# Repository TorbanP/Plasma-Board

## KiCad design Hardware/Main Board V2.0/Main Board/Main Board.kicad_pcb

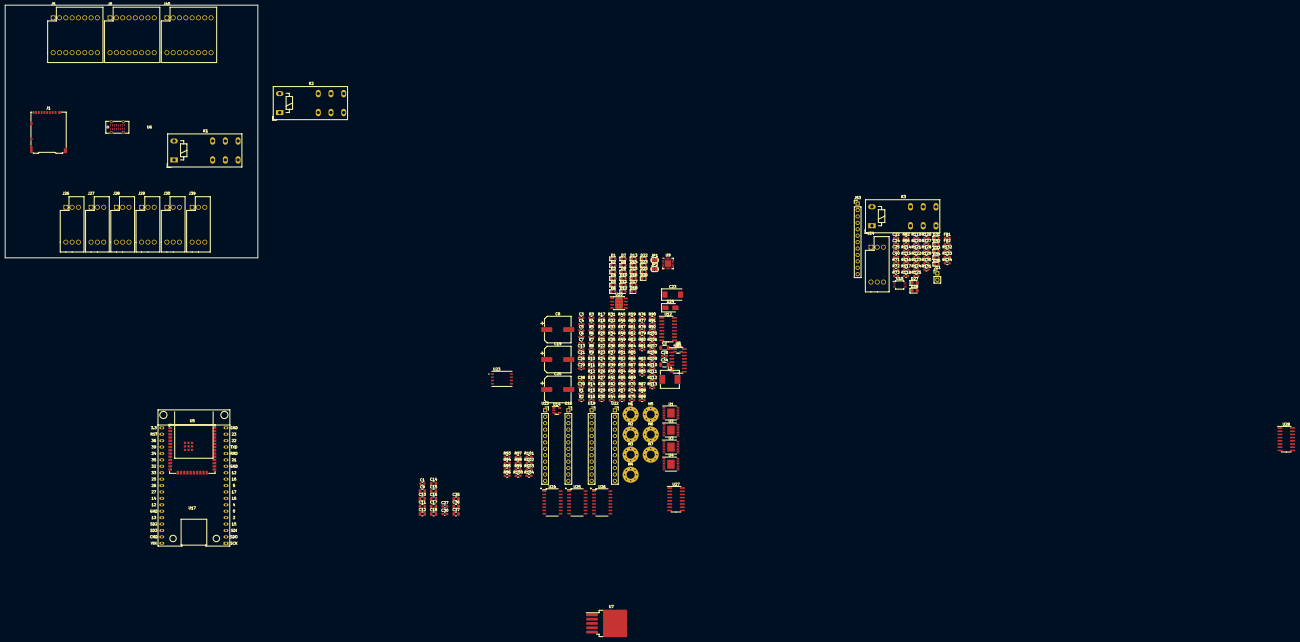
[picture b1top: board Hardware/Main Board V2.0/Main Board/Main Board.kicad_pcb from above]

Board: 2 copper layers, 100.0 x 100.0 mm, 254 parts (0 on the bottom side), 195 nets, no tracks yet.

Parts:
C1, C3, C4, C5, C6, C7, C13, C22, C24, C25, C26, C38, C40: 100nF; C_0603_1608Metric
C2, C34: 22uF; C_1206_3216Metric
C8, C19, C20: 120uF; CP_Elec_10x12.6
C9, C16, C36: 4.7uF; C_0805_2012Metric
C10, C12, C14, C15, C17, C35: 10uF; C_0805_2012Metric
C11, C18, C37: 1uF; C_0805_2012Metric
C21, C39: 10nF; C_0603_1608Metric
C23: 330uF; CP_EIA-7343-31_Kemet-D
C27: 22nf; C_0603_1608Metric_Pad1.08x0.95mm_HandSolder
C28, C30: 1uf; C_0603_1608Metric_Pad1.08x0.95mm_HandSolder
C29: 100nf; C_0603_1608Metric_Pad1.08x0.95mm_HandSolder
D1, D2, D3, D4, D5, D6, D7, D8, D9, D10, D11, D12, D13, D14, D15, D16, D17, D18, D22, D23, D25, D26, D31, D32, D33, D34, D35: Emerald; LED_0603_1608Metric
D24: SS54; D_SMA
D27, D28: MSCD104H; D_0805_2012Metric_Pad1.15x1.40mm_HandSolder
FB1, FB2: BLM18HE152SN1D; R_0603_1608Metric_Pad0.98x0.95mm_HandSolder
H1, H2, H3, H4, H5, H6, H7: MountingHole_3.2mm_M3_Pad_Via
J1: Micro_SD_Card; microSD_HC_Hirose_DM3AT-SF-PEJM5
J5, J8, J40: Conn_02x08_Top_Bottom; DB2ERH-2.5-2-8P-GN
J11: Conn_01x02_Male; PinHeader_1x02_P2.54mm_Vertical
J24, J26, J27, J28, J29, J30, J39: Conn_02x03_Top_Bottom; DB2ERH-2.5-2-3P-GN
J53: Module conn; PinHeader_1x12_P2.54mm_Vertical
JP1, JP2: SolderJumper_2_Bridged; SolderJumper-2_P1.3mm_Bridged_RoundedPad1.0x1.5mm
K1, K2, K3: G2RL-1-E-DC12; Relay_SPDT_Schrack-RT1-16A-FormC_RM5mm
L3: 15uH; L_Sunlord_MWSA0603S
R1, R2, R3, R4, R5, R6, R7, R8, R9, R10, R11, R12, R13, R14, R15, R16, R17, R18, R19, R20, R21, R50, R51, R79: 1K; R_0603_1608Metric
R22, R28, R29, R30, R31, R32, R33, R34, R35, R36, R37, R38, R39, R40, R41, R42, R43, R44, R45, R46, R47, R48, R49, R52, R53, R55, R71, R72, R80, R81, R82, R83, R86, R114, R115, R116, R117, R119, R120, R121, R122, R123, R124, R125, R126, R127, R128, R129, R130, R131: 10K; R_0603_1608Metric
R23, R54: 20R; R_0603_1608Metric
R24, R90, R91: 1K; R_0603_1608Metric_Pad0.98x0.95mm_HandSolder
R25: 120R; R_0603_1608Metric
R26: 24K; R_0603_1608Metric
R27: 47K; R_0603_1608Metric
R56, R57, R58, R59, R60, R61, R62, R63, R64, R65, R66, R67, R68, R69, R70, R105, R106, R107, R108, R109, R110, R111, R112, R113: 510R; R_0603_1608Metric
R73, R118: 5K; R_0603_1608Metric
R74, R75: 5.1K; R_0603_1608Metric
R76: 100K; R_0603_1608Metric
R77: 4.7K; R_0603_1608Metric
R78: 4.3K; R_0603_1608Metric
R84: 3.24K; R_0603_1608Metric
R85: 430R; R_0603_1608Metric
R87, R93, R94, R95, R96, R97, R98, R99, R100, R101, R102, R103, R104: 2K; R_0603_1608Metric_Pad0.98x0.95mm_HandSolder
R88, R89: 200; R_0603_1608Metric_Pad0.98x0.95mm_HandSolder
R92, R132, R133, R134: 2.4K; R_0603_1608Metric_Pad0.98x0.95mm_HandSolder
U1, U2, U3, U4: 74AHCT595PW; TSSOP-16-1EP_4.4x5mm_P0.65mm
U5: ESP32-WROOM-32UE-H4; ESP32-WROOM-32UE
U6: GT-USB-7051A
U7: LM2596S-12; TO-263-5_TabPin3
U8: AP2112K-3.3; SOT-23-5
U9: CP2104; QFN-24-1EP_4x4mm_P0.5mm_EP2.6x2.6mm
U10: TPS5430DDA; TI_SO-PowerPAD-8_ThermalVias
U11, U27, U28: ULN2003A; SOIC-16_3.9x9.9mm_P1.27mm
U12: 74LVC157A; SOP-16_3.9x9.9mm_P1.27mm
U13: Module A1; PinSocket_1x12_P2.54mm_Vertical
U14: NCV8114ASN150T1G; TSOT-23-5
U15: ADS1115IDGS; TSSOP-10_3x3mm_P0.5mm
U16: Module A2; PinSocket_1x12_P2.54mm_Vertical
U17: ESP32_38p; MH ET LIVE ESP-32 Dev Kit
U19: Module A3; PinSocket_1x12_P2.54mm_Vertical
U22: Module A4; PinSocket_1x12_P2.54mm_Vertical
U23: XTSD04GLGEAG; SON127P600X800X95-8N
U24, U25, U26: ELQ3H7; ELQ3H7 SOP-16_4.4x10.4mm_P1.27mm

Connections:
+3V3: C2.1, C3.1, C9.1, C11.1, C13.1, C15.1, C18.1, C22.1, J1.4 (VDD), R22.2, R28.2, R50.2, R51.2, R52.2, R55.2, R71.2, R72.2, R77.2, R78.2, R120.1, R121.1, R122.1, R123.1, R124.1, R125.1, R126.1, R127.1, R128.1, R129.1, R130.1, R131.1, U5.2 (3V3), U8.5 (VOUT), U9.5 (VIO), U9.6 (VDD), U9.7 (REGIN), U17.20 (3.3V), U23.8 (VDD)
+12V: C1.2, C2.2, C3.2, C4.1, C4.2, C5.1, C5.2, C6.1, C6.2, C7.1, C7.2, C8.2, C9.2, C10.1, C10.2, C11.2, C12.2, C13.2, C14.2, C15.2, C16.2, C17.2, C18.2, C19.2, C20.1, C20.2, C22.2, C23.1, C23.2, C24.2, C25.2, C26.1, C26.2, C40.2, D22.1 (K), D23.1 (K), D24.2 (A), D25.1 (K), D26.1 (K), H1.1, H2.1, H3.1, H4.1, H5.1, H6.1, H7.1, J1.6 (VSS), J1.9 (SHIELD), J24.3, J24.6, J26.1, J26.3, J26.4, J26.6, J27.1, J27.3, J27.4, J27.6, J28.1, J28.3, J28.4, J28.6, J29.1, J29.3, J29.4, J29.6, J30.1, J30.3, J30.4, J30.6, J39.1, J39.3, J39.4, J39.6, K1.A2, K2.A2, K3.A2, L3.2, R1.2, R2.2, R3.2, R4.2, R5.2, R6.2, R7.2, R8.2, R9.2, R10.2, R11.2, R12.2, R13.2, R14.2, R15.2, R16.2, R17.2, R18.2, R19.2, R20.2, R21.2, R27.1, R29.1, R30.1, R31.1, R32.1, R33.1, R34.1, R35.1, R36.1, R37.1, R38.1, R39.1, R40.1, R41.1, R42.1, R43.1, R44.1, R45.1, R46.1, R47.1, R48.1, R49.1, R53.1, R74.1, R75.1, R76.2, R79.2, R82.2, R83.2, R84.1, R85.2, R93.1, R94.1, R95.1, R96.1, R97.1, R98.1, R99.1, R100.1, R101.1, R102.1, R103.1, R104.1, R114.1, R115.1, R117.2, R119.1, U1.8 (GND), U1.10 (MR#), U1.13 (OE#), U1.16 (VCC), U2.8 (GND), U2.10 (MR#), U2.13 (OE#), U2.16 (VCC), U3.8 (GND), U3.10 (MR#), U3.13 (OE#), U3.16 (VCC), U4.8 (GND), U4.10 (MR#), U4.13 (OE#), U4.16 (VCC), U5.1 (GND), U5.15 (GND), U5.38 (GND), U5.39 (GND_THERMAL), U6.A1 (GND), U6.A12 (GND), U6.B1 (GND), U6.B12 (GND), U7.3 (GND), U7.5 (~ON/OFF), U8.1 (VIN), U8.2 (GND), U9.2 (GND), U9.25 (GND), U10.6 (GND), U10.9 (GNDPAD), U11.8 (GND), U11.9 (COM), U12.8 (GND), U12.15 (~EN), U12.16 (VCC), U13.1 (Gnd), U13.2 (VMot), U13.12 (Gnd), U16.1 (Gnd), U16.2 (VMot), U16.12 (Gnd), U17.13 (GND), U17.19 (GND), U17.33 (GND), U17.38 (VIN), U19.1 (Gnd), U19.2 (VMot), U19.12 (Gnd), U22.1 (Gnd), U22.2 (VMot), U22.12 (Gnd), U23.4 (VSS), U24.9, U24.11, U24.13, U24.15, U25.9, U25.11, U25.13, U25.15, U26.9, U26.11, U26.13, U26.15, U27.8 (GND), U27.9 (COM), U28.8 (GND), U28.9 (COM)
+24V: C8.1, C12.1, C14.1, C17.1, U7.1 (VIN), U10.7 (VIN)
A_Dir: R37.2, U2.4 (Q4), U11.6 (I6)
A_Dir_HV: D13.1 (K), J40.13, U11.11 (O6)
A_Enable: R39.2, U2.7 (Q7), U11.4 (I4)
A_Enable_HV: D11.1 (K), J40.9, U11.13 (O4)
A_LIM: R128.2, U5.10 (DAC_1/ADC2_CH8/GPIO25), U17.28 (IO25), U26.16
A_Step: R38.2, U2.5 (Q5), U11.5 (I5)
A_Step_HV: D12.1 (K), J40.11, U11.12 (O5)
B_Dir: R47.2, U3.1 (Q1), U28.3 (I3)
B_Dir_HV: D17.1 (K), J5.13, U28.14 (O3)
B_Enable: R49.2, U3.15 (Q0), U28.1 (I1)
B_Enable_HV: D15.1 (K), J5.9, U28.16 (O1)
B_LIM: R129.2, U5.11 (DAC_2/ADC2_CH9/GPIO26), U17.29 (IO26), U26.14
B_Step: R48.2, U3.2 (Q2), U28.2 (I2)
B_Step_HV: D16.1 (K), J5.11, U28.15 (O2)
CC1: R74.2, U6.A5 (CC1)
CC2: R75.2, U6.B5 (CC2)
CS_SD: J1.2 (DAT3/CD), U5.23 (MTDO/GPIO15/ADC2_CH3), U17.4 (IO15), U23.6 (SD0/DO)
C_Dir: R44.2, U3.4 (Q4), U28.6 (I6)
C_Dir_HV: D32.1 (K), J8.13, U28.11 (O6)
C_Enable: R46.2, U3.7 (Q7), U28.4 (I4)
C_Enable_HV: D18.1 (K), J8.9, U28.13 (O4)
C_LIM: R130.2, U5.12 (ADC2_CH7/GPIO27), U17.30 (IO27), U26.12
C_Step: R45.2, U3.5 (Q5), U28.5 (I5)
C_Step_HV: D31.1 (K), J8.11, U28.12 (O5)
D+: U6.A6 (DP1), U6.B6 (DP2), U9.3 (D+)
D-: U6.A7 (DN1), U6.B7 (DN2), U9.4 (D-)
DTR: R81.1, U9.23 (~DTR)
EXT_MUX_EN: R119.2, U12.1 (S)
GPI_0: C24.1, JP1.2 (B), R22.1, R120.2, U5.25 (GPIO0/BOOT/ADC2_CH1), U17.6 (IO0), U24.16
I2S_BCK: U1.11 (SHCP), U2.11 (SHCP), U3.11 (SHCP), U4.11 (SHCP), U5.37 (GPIO23), U17.18 (IO23)
I2S_DATA: U1.14 (DS), U5.36 (GPIO22), U17.17 (IO22)
I2S_WS: U1.12 (STCP), U2.12 (STCP), U3.12 (STCP), U4.12 (STCP), U5.33 (GPIO21), U17.14 (IO21)
MACRO_1: R122.2, U5.4 (SENSOR_VP/GPIO36/ADC1_CH0), U17.22 (IO36), U24.12
MACRO_2: R123.2, U5.5 (SENSOR_VN/GPIO39/ADC1_CH3), U17.23 (IO39), U24.10
MACRO_3: R124.2, U5.6 (GPIO34/ADC1_CH6), U17.24 (IO34), U25.16
MISO: J1.7 (DAT0), U5.14 (MTDI/GPIO12/ADC2_CH5), U17.32 (IO12)
MOSI: J1.3 (CMD), U5.16 (MTCK/GPIO13/ADC2_CH4), U17.34 (IO13), U23.5 (CMD/DI)
unnamed: D1.2 (A), R10.1
unnamed: D2.2 (A), R1.1
unnamed: D3.2 (A), R2.1
unnamed: D4.2 (A), R3.1
unnamed: D5.2 (A), R4.1
unnamed: D6.2 (A), R5.1
unnamed: D7.2 (A), R6.1
unnamed: D8.2 (A), R7.1
unnamed: D9.2 (A), R8.1
unnamed: D10.2 (A), R9.1
unnamed: D11.2 (A), R11.1
unnamed: D12.2 (A), R12.1
unnamed: D13.2 (A), R13.1
unnamed: D14.2 (A), R14.1
unnamed: D15.2 (A), R15.1
unnamed: D16.2 (A), R16.1
unnamed: D17.2 (A), R17.1
unnamed: D18.2 (A), R18.1
unnamed: U6.A4 (VBUS), U6.A9 (VBUS), U6.B4 (VBUS), U6.B9 (VBUS)
unnamed: D22.2 (A), R78.1
unnamed: D23.2 (A), R79.1
unnamed: C21.2, D24.1 (K), L3.1, U10.8 (PH)
unnamed: D25.2 (A), R85.1
unnamed: D27.2 (A), R24.1, R88.2
unnamed: C29.1, D27.1 (K), FB2.1, R132.1, R133.1, R134.1, U14.1 (IN), U14.3 (EN), U15.8 (VDD)
unnamed: C28.2, C29.2, D28.2 (A), FB1.2, R92.2, U14.2 (GND), U15.3 (GND)
unnamed: D28.1 (K), R87.2, R89.2
unnamed: D31.2 (A), R19.1
unnamed: D32.2 (A), R20.1
unnamed: D33.2 (A), R21.1
unnamed: D34.2 (A), R50.1
unnamed: D35.2 (A), R51.1
unnamed: J24.4, R23.1
unnamed: J24.5, R54.1
unnamed: R106.1, R107.1, R108.1, R109.1
unnamed: R110.1, R111.1, R112.1, R113.1
unnamed: R56.1, R57.1, R58.1, R105.1
unnamed: J5.2, R106.2
unnamed: J5.4, R107.2
unnamed: J5.6, R108.2
unnamed: J5.8, R109.2
unnamed: J5.10, R63.2
unnamed: J5.12, R64.2
unnamed: J5.14, R65.2
unnamed: J5.16, R66.2
unnamed: R59.1, R60.1, R61.1, R62.1
unnamed: R63.1, R64.1, R65.1, R66.1
unnamed: J8.2, R110.2
unnamed: J8.4, R111.2
unnamed: J8.6, R112.2
unnamed: J8.8, R113.2
unnamed: J8.10, R59.2
unnamed: J8.12, R60.2
unnamed: J8.14, R61.2
unnamed: J8.16, R62.2
unnamed: J11.1, R24.2
unnamed: J11.2, R87.1
unnamed: J26.2, U24.8
unnamed: J26.5, U24.6
unnamed: J27.2, U25.4
unnamed: J27.5, U25.2
unnamed: J28.2, U25.8
unnamed: J28.5, U25.6
unnamed: J29.2, U26.4
unnamed: J29.5, U26.2
unnamed: J30.2, U26.8
unnamed: J30.5, U26.6
unnamed: R67.1, R68.1, R69.1, R70.1
unnamed: J39.2, U24.4
unnamed: J39.5, U24.2
unnamed: J40.2, R56.2
unnamed: J40.4, R57.2
unnamed: J40.6, R58.2
unnamed: J40.8, R105.2
unnamed: J40.10, R67.2
unnamed: J40.12, R68.2
unnamed: J40.14, R69.2
unnamed: J40.16, R70.2
unnamed: C30.2, FB1.1, J53.1, J53.12
unnamed: C30.1, FB2.2, J53.3
unnamed: J53.9, R134.2, U15.2 (ALERT/RDY)
unnamed: J53.10, R132.2, U15.9 (SDA)
unnamed: J53.11, R133.2, U15.10 (SCL)
unnamed: R93.2, U24.1
unnamed: R94.2, U24.3
unnamed: R95.2, U24.5
unnamed: R96.2, U24.7
unnamed: R97.2, U25.1
unnamed: R98.2, U25.3
unnamed: R99.2, U25.5
unnamed: R100.2, U25.7
unnamed: R101.2, U26.1
unnamed: R102.2, U26.3
unnamed: R103.2, U26.5
unnamed: R104.2, U26.7
unnamed: R131.2, U26.10
unnamed: U1.9 (Q7S), U2.14 (DS)
unnamed: U2.9 (Q7S), U3.14 (DS)
unnamed: U3.9 (Q7S), U4.14 (DS)
unnamed: C19.1, U7.4 (FB)
unnamed: R76.1, U8.3 (EN)
unnamed: R26.1, R27.2, U9.8 (VBUS)
unnamed: C16.1, U9.16 (VPP)
unnamed: R77.1, U9.9 (~RST)
unnamed: C21.1, U10.1 (BOOT)
unnamed: R83.1, R84.2, U10.4 (VSENSE)
unnamed: C28.1, R90.1, R91.2, U14.5 (OUT)
unnamed: R92.1, U15.1 (ADDR)
unnamed: C27.1, R88.1, R90.2, U15.4 (AIN0)
unnamed: C27.2, R89.1, R91.1, U15.5 (AIN1)
unnamed: R25.1, R53.2, R54.2
unnamed: R23.2, R25.2, R52.1
unnamed: C1.1, R86.2
unnamed: R73.2, R82.1
unnamed: C40.1, R116.2
unnamed: R117.1, R118.2
PWM1: R86.1, R114.2, U5.24 (ADC2_CH2/GPIO2), U17.5 (IO2)
PWM2: R115.2, R116.1, U5.26 (ADC2_CH0/GPIO4), U17.7 (IO4)
RESET: C25.1, JP2.2 (B), R28.1, R121.2, U5.3 (EN/CHIP_PU), U17.21 (RST), U24.14
RLY_1: R29.2, U1.3 (Q3), U27.7 (I7)
RLY_1_HV: D7.1 (K), K2.A1, U27.10 (O7)
RLY_2: R36.2, U2.6 (Q6), U11.7 (I7)
RLY_2_HV: D14.1 (K), K1.A1, U11.10 (O7)
RLY_3: R43.2, U2.3 (Q3), U28.7 (I7)
RLY_3_HV: K3.A1, U28.10 (O7)
RS485_EN: R72.1, U5.29 (GPIO5), U17.10 (IO5)
RS485_RX: D35.1 (K), R71.1, U5.27 (GPIO16), U17.8 (IO16)
RS485_TX: D34.1 (K), R55.1, U5.28 (GPIO17), U17.9 (IO17)
RTS: R80.1, U9.19 (~RTS)
RXD0: U5.34 (U0RXD/GPIO3), U9.21 (TXD), U17.15 (RXD)
SCL: U5.31 (GPIO19), U17.12 (IO19)
SCLK: J1.5 (CLK), U5.13 (MTMS/GPIO14/ADC2_CH6), U17.31 (IO14), U23.3 (CLK)
SDA: U5.30 (GPIO18), U17.11 (IO18)
TXD0: U5.35 (U0TXD/GPIO1), U9.20 (RXD), U17.16 (TXD)
X_Dir: R33.2, U1.1 (Q1), U27.3 (I3)
X_Dir_HV: D3.1 (K), J40.5, U27.14 (O3)
X_Enable: R35.2, U1.15 (Q0), U27.1 (I1)
X_Enable_HV: D1.1 (K), J40.1, U27.16 (O1)
X_LIM: R125.2, U5.7 (GPIO35/ADC1_CH7), U17.25 (IO35), U25.14
X_Step: R34.2, U1.2 (Q2), U27.2 (I2)
X_Step_HV: D2.1 (K), J40.3, U27.15 (O2)
Y_Dir: R30.2, U1.4 (Q4), U27.6 (I6)
Y_Dir_HV: D6.1 (K), J5.5, U27.11 (O6)
Y_Enable: R32.2, U1.7 (Q7), U27.4 (I4)
Y_Enable_HV: D4.1 (K), J5.1, U27.13 (O4)
Y_LIM: R126.2, U5.8 (32K_XP/GPIO32/ADC1_CH4), U17.26 (IO32), U25.12
Y_Step: R31.2, U1.5 (Q5), U27.5 (I5)
Y_Step_HV: D5.1 (K), J5.3, U27.12 (O5)
Z_Dir: R40.2, U2.1 (Q1), U11.3 (I3), U12.7 (Qb), U12.11 (I0c)
Z_Dir_HV: D10.1 (K), J8.5, U11.14 (O3)
Z_Enable: R42.2, U2.15 (Q0), U11.1 (I1), U12.2 (I0a), U12.4 (Qa)
Z_Enable_HV: D8.1 (K), J8.1, U11.16 (O1)
Z_LIM: R127.2, U5.9 (32K_XN/GPIO33/ADC1_CH5), U17.27 (IO33), U25.10
Z_Step: R41.2, U2.2 (Q2), U11.2 (I2), U12.5 (I0b), U12.9 (Qc)
Z_Step_HV: D9.1 (K), J8.3, U11.15 (O2)

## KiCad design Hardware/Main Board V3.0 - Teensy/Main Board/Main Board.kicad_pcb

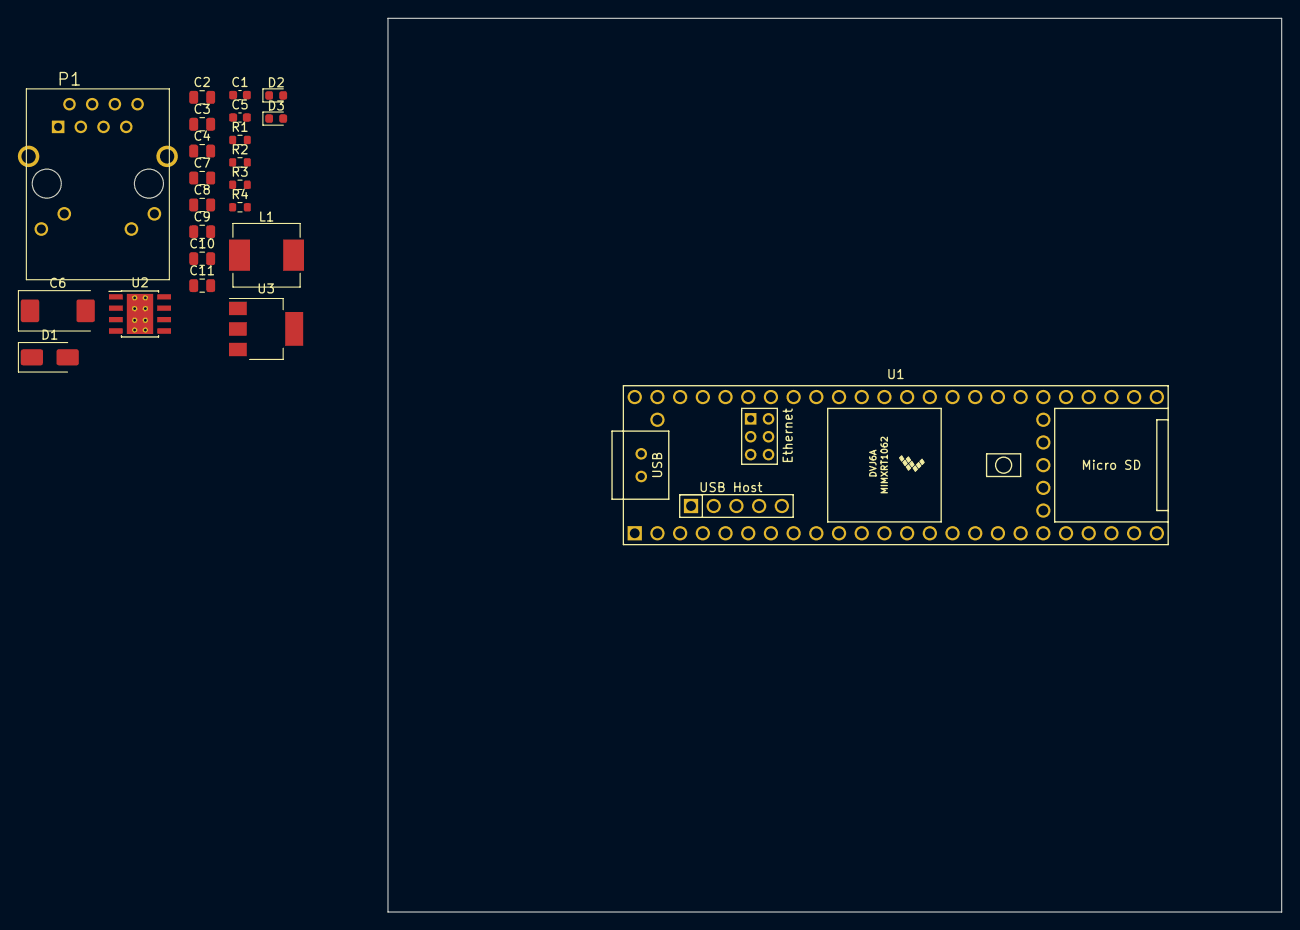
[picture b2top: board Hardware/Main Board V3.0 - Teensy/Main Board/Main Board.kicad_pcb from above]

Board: 2 copper layers, 100.0 x 100.0 mm, 23 parts (0 on the bottom side), 15 nets, no tracks yet.

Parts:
C1: 100nF; C_0603_1608Metric
C2, C3, C4, C7, C8: 10uF; C_0805_2012Metric
C5: 10nF; C_0603_1608Metric
C6: 330uF; CP_EIA-7343-31_Kemet-D
C9, C10: 1uF; C_0805_2012Metric
C11: 4.7uF; C_0805_2012Metric
D1: SS54; D_SMA
D2, D3: Emerald; LED_0603_1608Metric
L1: 15uH; L_Sunlord_MWSA0603S
P1: J1B1211CCD
R1: 10K; R_0603_1608Metric
R2: 3.24K; R_0603_1608Metric
R3: 430R; R_0603_1608Metric
R4: 4.3K; R_0603_1608Metric
U1: Teensy4.1; Teensy41
U2: TPS5430DDA; TI_SO-PowerPAD-8_ThermalVias
U3: AZ1117EH-3.3TRG1; SOT-223-3_TabPin2

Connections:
+3V3: C8.1, C9.1, R4.2, U1.15 (3V3), U1.46 (3V3), U3.2 (VO)
+5V: C6.1, C7.1, L1.2, R1.2, R3.2, U1.48 (VIN), U3.3 (VI)
+24V: C2.1, C3.1, C4.1, U2.7 (VIN)
ETH_LED: P1.10 (GRN+), U1.61 (LED)
ETH_RX+: P1.4 (RD+), U1.60 (R+)
ETH_RX-: P1.6 (RD-), U1.65 (R-)
ETH_TX+: P1.1 (TD+), U1.63 (T+)
ETH_TX-: P1.3 (TD-), U1.62 (T-)
GND: C1.2, C2.2, C3.2, C4.2, C6.2, C7.2, C8.2, C9.2, D1.2 (A), D2.1 (K), D3.1 (K), P1.8 (GH_GND@1), P1.9 (GRN-), P1.11 (YLW-), P1.13 (CH_GND@2), P1.14 (CH_GND@3), R2.1, U1.1 (GND), U1.34 (GND), U1.47 (GND), U1.52 (GND), U1.58 (GND), U1.59 (GND), U1.64 (GND), U2.6 (GND), U2.9 (GNDPAD), U3.1 (GND)
unnamed: C5.2, D1.1 (K), L1.1, U2.8 (PH)
unnamed: D2.2 (A), R3.1
unnamed: D3.2 (A), R4.1
unnamed: C1.1, P1.2 (TCT), P1.5 (RCT)
unnamed: C5.1, U2.1 (BOOT)
unnamed: R1.1, R2.2, U2.4 (VSENSE)

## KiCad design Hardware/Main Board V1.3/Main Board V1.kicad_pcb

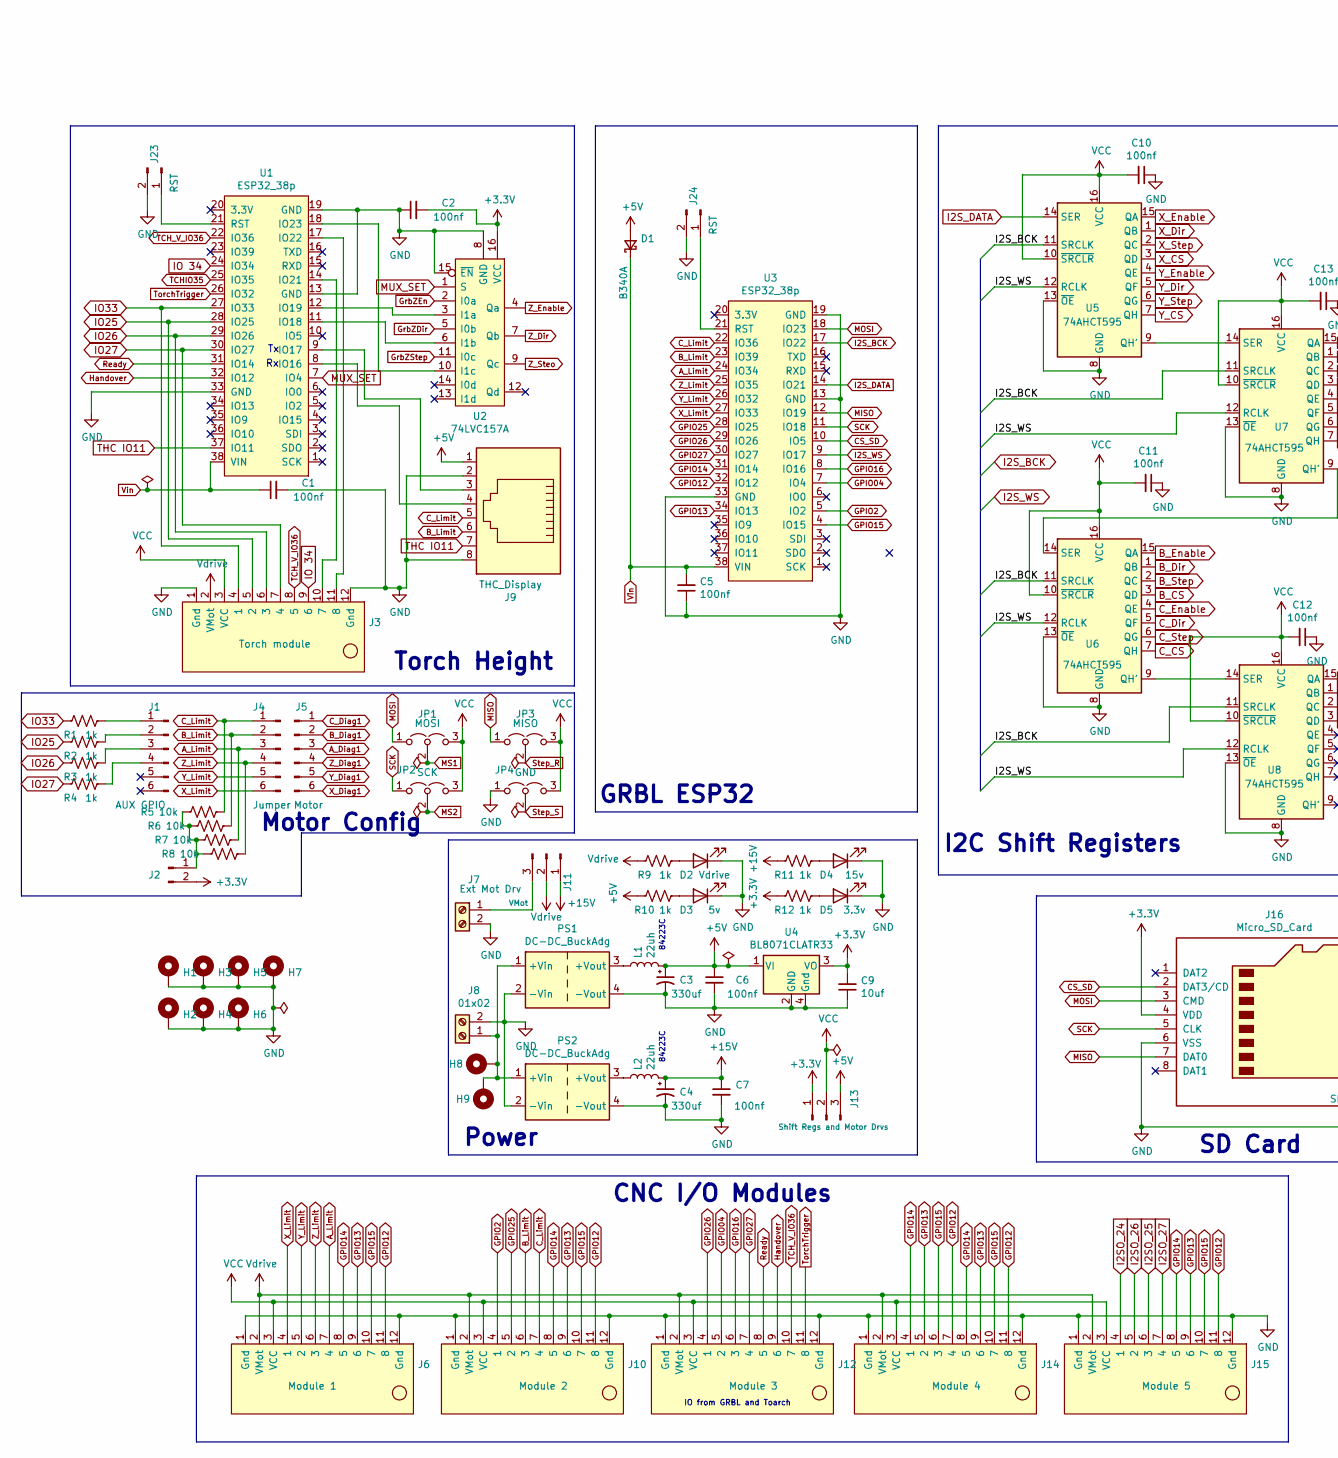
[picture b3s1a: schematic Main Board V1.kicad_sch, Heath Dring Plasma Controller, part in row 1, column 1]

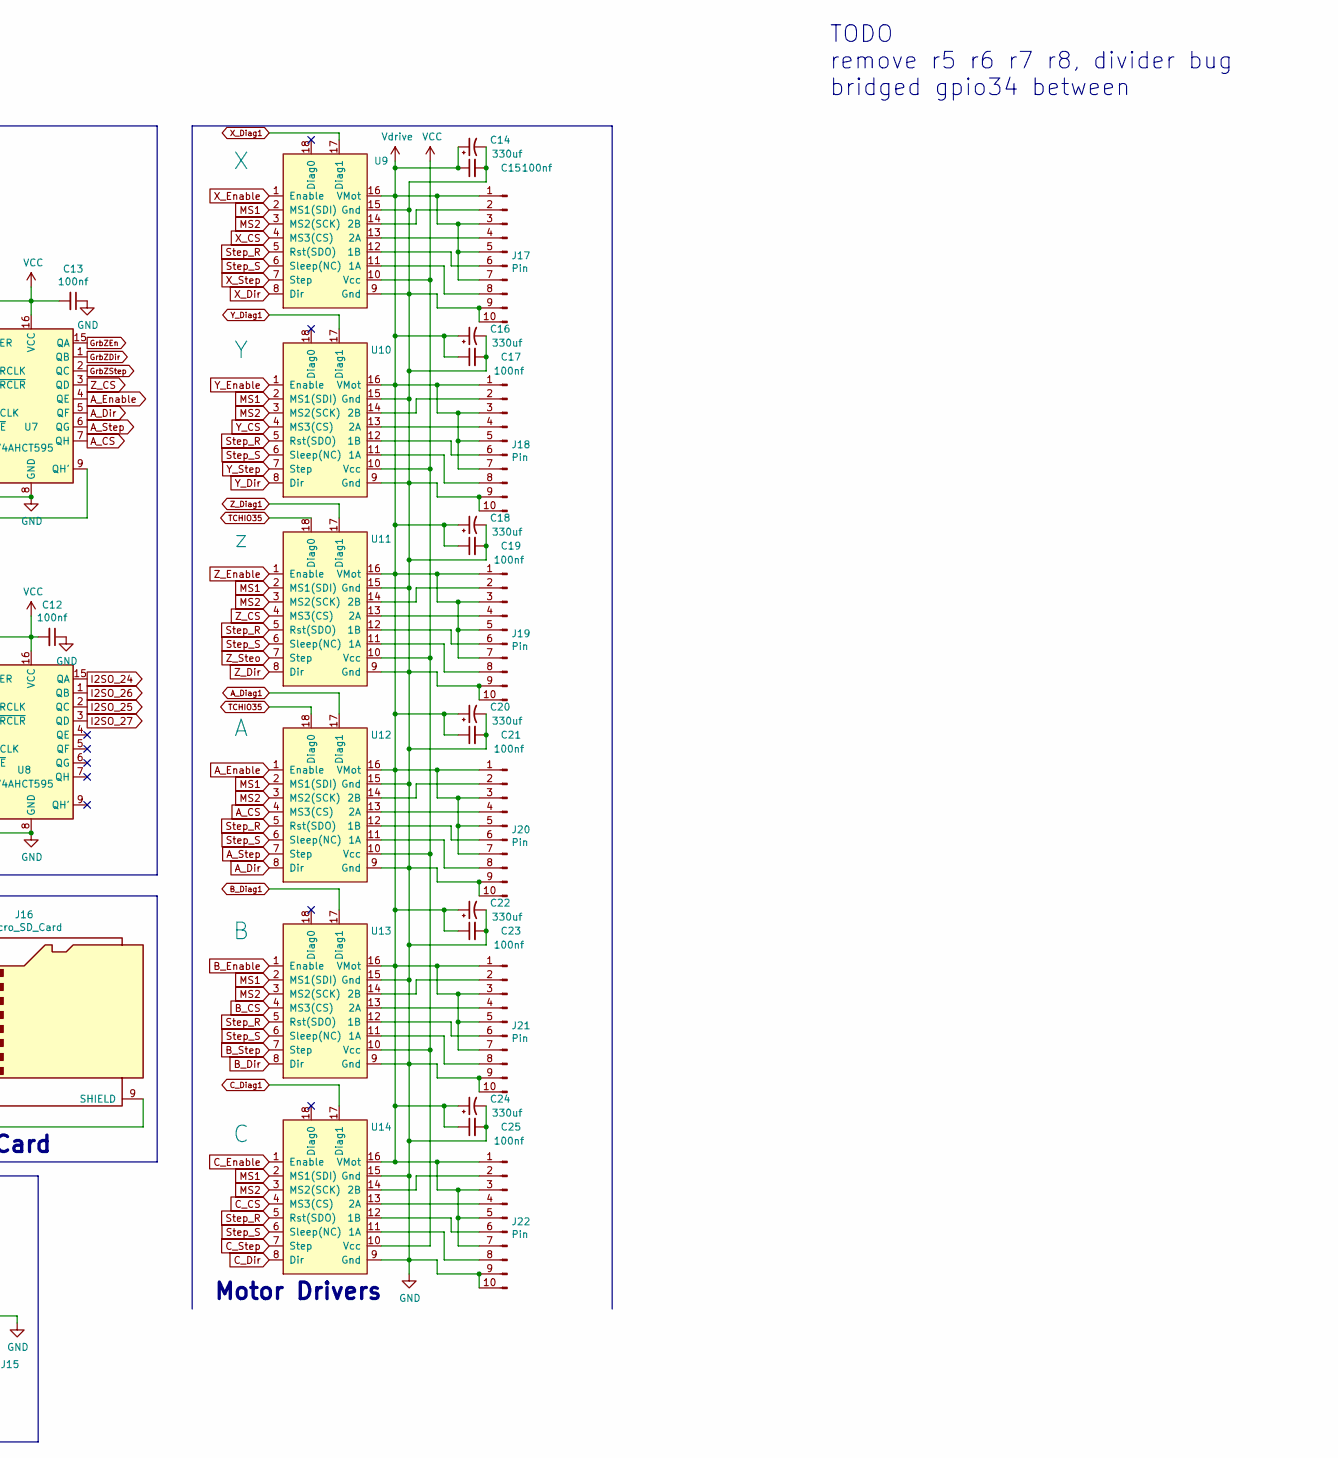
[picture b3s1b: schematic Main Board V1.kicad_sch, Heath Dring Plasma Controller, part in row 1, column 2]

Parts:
C1, C2, C5, C6, C7, C10, C11, C12, C13, C15, C17, C19, C21, C23, C25: 100nf; C_0603_1608Metric_Pad1.08x0.95mm_HandSolder; Part Number 0603B104M250CT; LCSC C107569
C3, C4, C14, C16, C18, C20, C22, C24: 330uf; CP_Elec_10x12.6; Part Number OCV331M1DTR-1013; LCSC C250026
C9: 10uf; C_0603_1608Metric_Pad1.08x0.95mm_HandSolder; Part Number GRM188R61E106KA73D; LCSC C344022
D1: B340A; D_0805_2012Metric_Pad1.15x1.40mm_HandSolder; Part Number MSCD104H; LCSC C189958
D2: Vdrive; D_0603_1608Metric_Pad1.05x0.95mm_HandSolder; Part Number NCD0603R1; LCSC C84263
D3: 5v; D_0603_1608Metric_Pad1.05x0.95mm_HandSolder; Part Number NCD0603R1; LCSC C84263
D4: 15v; D_0603_1608Metric_Pad1.05x0.95mm_HandSolder; Part Number NCD0603R1; LCSC C84263
D5: 3.3v; D_0603_1608Metric_Pad1.05x0.95mm_HandSolder; Part Number NCD0603R1; LCSC C84263
H1, H2, H3, H4, H5, H6, H7: MountingHole_2.7mm_M2.5_DIN965_Pad_TopBottom
H8, H9: Pin_D0.9mm_L10.0mm_W2.4mm_FlatFork
J1: AUX GPIO; PinHeader_1x06_P2.54mm_Vertical
J2: PinHeader_1x02_P2.54mm_Vertical
J3: Torch module; PinSocket_1x12_P2.54mm_Vertical
J4: Jumper; PinHeader_1x06_P2.54mm_Vertical
J5: Motor; PinHeader_1x06_P2.54mm_Vertical
J6: Module 1; PinSocket_1x12_P2.54mm_Vertical
J7: Ext Mot Drv; TerminalBlock_4Ucon_1x02_P3.50mm_Horizontal; Part Number JL124D-35002G01; LCSC C415432
J8: 01x02; TerminalBlock_4Ucon_1x02_P3.50mm_Horizontal; Part Number JL124D-35002G01; LCSC C415432
J9: THC_Display; RJ45_OST_PJ012-8P8CX_Vertical
J10: Module 2; PinSocket_1x12_P2.54mm_Vertical
J11: VMot; PinHeader_1x03_P2.54mm_Vertical
J12: Module 3; PinSocket_1x12_P2.54mm_Vertical
J13: Shift Regs and Motor Drvs; PinHeader_1x03_P2.54mm_Vertical
J14: Module 4; PinSocket_1x12_P2.54mm_Vertical
J15: Module 5; PinSocket_1x12_P2.54mm_Vertical
J16: Micro_SD_Card; microSD_HC_Hirose_DM3AT-SF-PEJM5; Part Number DM3AT-SF-PEJM5; LCSC C114218
J17, J18, J19, J20, J21, J22: Pin; PinHeader_2x05_P2.54mm_Vertical
J23, J24: RST; PinHeader_1x02_P2.54mm_Vertical
JP1: MOSI; PinHeader_1x03_P2.54mm_Vertical
JP2: SCK; PinHeader_1x03_P2.54mm_Vertical
JP3: MISO; PinHeader_1x03_P2.54mm_Vertical
JP4: GND; PinHeader_1x03_P2.54mm_Vertical
L1, L2: 22uh; L_Coilcraft_XAL5030; Part Number GCNR4030-220MC; LCSC C439349
PS1, PS2: DC-DC_BuckAdg; Buck_Module
R1, R2, R3, R4, R9, R10, R11, R12: 1k; R_0603_1608Metric_Pad0.98x0.95mm_HandSolder; LCSC C22548
R5, R6, R7, R8: 10k; R_0603_1608Metric_Pad0.98x0.95mm_HandSolder; LCSC C144081
U1, U3: ESP32_38p
U2: 74LVC157A; SOP-16_3.9x9.9mm_P1.27mm; Part Number XL74LS157; LCSC C707097
U4: BL8071CLATR33; SOT-223; Part Number BL8071CLATR33; LCSC C401677
U5, U6, U7, U8: 74AHCT595; SO-16_5.3x10.2mm_P1.27mm; Part Number 74AHCT595D,118; LCSC C503428
U9: X; ClearpathDriver
U10: Y; ClearpathDriver
U11: z; ClearpathDriver
U12: A; ClearpathDriver
U13: B; ClearpathDriver
U14: C; ClearpathDriver

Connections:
+3V3: C2.2, C9.2, J2.2, J13.1, J16.4 (VDD), R12.2, U2.16 (VCC), U4.3 (VO)
+5V: C3.1, C6.1, D1.2 (A), J9.1, J13.3, L1.2, R10.2, U4.1 (VI)
+15V: C4.1, C7.1, J11.1, L2.2, R11.2
A_CS: U7.7 (QH), U12.4 (MS3(CS))
A_Diag1: J5.3, U12.17 (Diag1)
A_Dir: U7.5 (QF), U12.8 (Dir)
A_Enable: U7.4 (QE), U12.1 (Enable)
A_Limit: J4.3, J6.7 (4), R7.1, U3.24 (IO34)
A_Step: U7.6 (QG), U12.7 (Step)
B_CS: U6.3 (QD), U13.4 (MS3(CS))
B_Diag1: J5.2, U13.17 (Diag1)
B_Dir: U6.1 (QB), U13.8 (Dir)
B_Enable: U6.15 (QA), U13.1 (Enable)
B_Limit: J4.2, J9.6, J10.6 (3), R6.1, U3.23 (IO39)
B_Step: U6.2 (QC), U13.7 (Step)
CS_SD: J16.2 (DAT3/CD), U3.10 (IO5)
C_CS: U6.7 (QH), U14.4 (MS3(CS))
C_Diag1: J5.1, U14.17 (Diag1)
C_Dir: U6.5 (QF), U14.8 (Dir)
C_Enable: U6.4 (QE), U14.1 (Enable)
C_Limit: J4.1, J9.5, J10.7 (4), R5.1, U3.22 (IO36)
C_Step: U6.6 (QG), U14.7 (Step)
GND: C1.2, C2.1, C3.2, C4.2, C5.1, C6.2, C7.2, C9.1, C10.1, C11.1, C12.1, C13.1, C14.2, C15.2, C16.2, C17.2, C18.2, C19.2, C20.2, C21.2, C22.2, C23.2, C24.2, C25.2, D2.1 (K), D3.1 (K), D4.1 (K), D5.1 (K), H1.1, H2.1, H3.1, H4.1, H5.1, H6.1, H7.1, J3.1 (Gnd), J3.12 (Gnd), J6.1 (Gnd), J6.12 (Gnd), J7.2, J8.2, J9.2, J9.8, J10.1 (Gnd), J10.12 (Gnd), J12.1 (Gnd), J12.12 (Gnd), J14.1 (Gnd), J14.12 (Gnd), J15.1 (Gnd), J15.12 (Gnd), J16.6 (VSS), J16.9 (SHIELD), J17.9, J17.10, J18.9, J18.10, J19.9, J19.10, J20.9, J20.10, J21.9, J21.10, J22.9, J22.10, J23.2, J24.2, JP4.1 (A), PS1.2 (-Vin), PS1.4 (-Vout), PS2.2 (-Vin), PS2.4 (-Vout), U1.13 (GND), U1.19 (GND), U1.33 (GND), U2.8 (GND), U2.15 (~EN), U3.13 (GND), U3.19 (GND), U3.33 (GND), U4.2 (GND), U4.4 (Gnd), U5.8 (GND), U5.13 (~OE), U6.8 (GND), U6.13 (~OE), U7.8 (GND), U7.13 (~OE), U8.8 (GND), U8.13 (~OE), U9.9 (Gnd), U9.15 (Gnd), U10.9 (Gnd), U10.15 (Gnd), U11.9 (Gnd), U11.15 (Gnd), U12.9 (Gnd), U12.15 (Gnd), U13.9 (Gnd), U13.15 (Gnd), U14.9 (Gnd), U14.15 (Gnd)
GPIO2: J10.4 (1), U3.5 (IO2)
GPIO04: J12.5 (2), U3.7 (IO4)
GPIO12: J6.11 (8), J10.11 (8), J14.7 (4), J14.11 (8), J15.11 (8), U3.32 (IO12)
GPIO13: J6.9 (6), J10.9 (6), J14.5 (2), J14.9 (6), J15.9 (6), U3.34 (IO13)
GPIO14: J6.8 (5), J10.8 (5), J14.4 (1), J14.8 (5), J15.8 (5), U3.31 (IO14)
GPIO15: J6.10 (7), J10.10 (7), J14.6 (3), J14.10 (7), J15.10 (7), U3.4 (IO15)
GPIO16: J12.6 (3), U3.8 (IO16)
GPIO25: J10.5 (2), U3.28 (IO25)
GPIO26: J12.4 (1), U3.29 (IO26)
GPIO27: J12.7 (4), U3.30 (IO27)
GrbZDir: U2.5 (I0b), U7.1 (QB)
GrbZEn: U2.2 (I0a), U7.15 (QA)
GrbZStep: U2.11 (I0c), U7.2 (QC)
Handover: J12.9 (6), U1.32 (IO12)
I2SO_24: J15.4 (1), U8.15 (QA)
I2SO_25: J15.6 (3), U8.2 (QC)
I2SO_26: J15.5 (2), U8.1 (QB)
I2SO_27: J15.7 (4), U8.3 (QD)
I2S_BCK: U3.17 (IO22), U5.11 (SRCLK), U6.11 (SRCLK), U7.11 (SRCLK), U8.11 (SRCLK)
I2S_DATA: U3.14 (IO21), U5.14 (SER)
I2S_WS: U3.9 (IO17), U5.12 (RCLK), U6.12 (RCLK), U7.12 (RCLK), U8.12 (RCLK)
IO25: J3.5 (2), R2.2, U1.28 (IO25)
IO26: J3.6 (3), R3.2, U1.29 (IO26)
IO27: J3.7 (4), R4.2, U1.30 (IO27)
IO33: J3.4 (1), R1.2, U1.27 (IO33)
IO 34: J3.9 (6), U1.24 (IO34)
MISO: J16.7 (DAT0), JP3.1 (A), U3.12 (IO19)
MOSI: J16.3 (CMD), JP1.1 (A), U3.18 (IO23)
MS1: JP1.2 (C), U9.2 (MS1(SDI)), U10.2 (MS1(SDI)), U11.2 (MS1(SDI)), U12.2 (MS1(SDI)), U13.2 (MS1(SDI)), U14.2 (MS1(SDI))
MS2: JP2.2 (C), U9.3 (MS2(SCK)), U10.3 (MS2(SCK)), U11.3 (MS2(SCK)), U12.3 (MS2(SCK)), U13.3 (MS2(SCK)), U14.3 (MS2(SCK))
MUX_SET: U1.7 (IO4), U2.1 (S)
unnamed: D2.2 (A), R9.1
unnamed: D3.2 (A), R10.1
unnamed: D4.2 (A), R11.1
unnamed: D5.2 (A), R12.1
unnamed: J1.1, R1.1
unnamed: J1.2, R2.1
unnamed: J1.3, R3.1
unnamed: J1.4, R4.1
unnamed: J2.1, R5.2, R6.2, R7.2, R8.2
unnamed: J3.10 (7), U1.14 (IO21)
unnamed: J3.11 (8), U1.17 (IO22)
unnamed: H8.1, H9.1, J8.1, PS1.1 (+Vin), PS2.1 (+Vin)
unnamed: J7.1, J11.3
unnamed: J17.2, U9.14 (2B)
unnamed: J17.4, U9.13 (2A)
unnamed: J17.6, U9.12 (1B)
unnamed: J17.8, U9.11 (1A)
unnamed: J18.2, U10.14 (2B)
unnamed: J18.4, U10.13 (2A)
unnamed: J18.6, U10.12 (1B)
unnamed: J18.8, U10.11 (1A)
unnamed: J19.2, U11.14 (2B)
unnamed: J19.4, U11.13 (2A)
unnamed: J19.6, U11.12 (1B)
unnamed: J19.8, U11.11 (1A)
unnamed: J20.2, U12.14 (2B)
unnamed: J20.4, U12.13 (2A)
unnamed: J20.6, U12.12 (1B)
unnamed: J20.8, U12.11 (1A)
unnamed: J21.2, U13.14 (2B)
unnamed: J21.4, U13.13 (2A)
unnamed: J21.6, U13.12 (1B)
unnamed: J21.8, U13.11 (1A)
unnamed: J22.2, U14.14 (2B)
unnamed: J22.4, U14.13 (2A)
unnamed: J22.6, U14.12 (1B)
unnamed: J22.8, U14.11 (1A)
unnamed: J23.1, U1.21 (RST)
unnamed: J24.1, U3.21 (RST)
unnamed: L1.1, PS1.3 (+Vout)
unnamed: L2.1, PS2.3 (+Vout)
unnamed: J9.4, U1.8 (IO16)
unnamed: J9.3, U1.9 (IO17)
unnamed: U1.11 (IO18), U2.6 (I1b)
unnamed: U1.12 (IO19), U2.3 (I1a)
unnamed: U1.18 (IO23), U2.10 (I1c)
unnamed: U5.9 (QH'), U7.14 (SER)
unnamed: U6.9 (QH'), U8.14 (SER)
unnamed: U6.14 (SER), U7.9 (QH')
Ready: J12.8 (5), U1.31 (IO14)
SCK: J16.5 (CLK), JP2.1 (A), U3.11 (IO18)
Step_R: JP3.2 (C), U9.5 (Rst(SDO)), U10.5 (Rst(SDO)), U11.5 (Rst(SDO)), U12.5 (Rst(SDO)), U13.5 (Rst(SDO)), U14.5 (Rst(SDO))
Step_S: JP4.2 (C), U9.6 (Sleep(NC)), U10.6 (Sleep(NC)), U11.6 (Sleep(NC)), U12.6 (Sleep(NC)), U13.6 (Sleep(NC)), U14.6 (Sleep(NC))
TCHIO35: U1.25 (IO35), U11.18 (Diag0), U12.18 (Diag0)
TCH_V_IO36: J3.8 (5), J12.10 (7), U1.22 (IO36)
THC IO11: J9.7, U1.37 (IO11)
TorchTrigger: J12.11 (8), U1.26 (IO32)
VCC: C10.2, C11.2, C12.2, C13.2, J3.3 (VCC), J6.3 (VCC), J10.3 (VCC), J12.3 (VCC), J13.2, J14.3 (VCC), J15.3 (VCC), JP1.3 (B), JP2.3 (B), JP3.3 (B), JP4.3 (B), U5.10 (~SRCLR), U5.16 (VCC), U6.10 (~SRCLR), U6.16 (VCC), U7.10 (~SRCLR), U7.16 (VCC), U8.10 (~SRCLR), U8.16 (VCC), U9.10 (Vcc), U10.10 (Vcc), U11.10 (Vcc), U12.10 (Vcc), U13.10 (Vcc), U14.10 (Vcc)
Vdrive: C14.1, C15.1, C16.1, C17.1, C18.1, C19.1, C20.1, C21.1, C22.1, C23.1, C24.1, C25.1, J3.2 (VMot), J6.2 (VMot), J10.2 (VMot), J11.2, J12.2 (VMot), J14.2 (VMot), J15.2 (VMot), J17.1, J17.3, J17.5, J17.7, J18.1, J18.3, J18.5, J18.7, J19.1, J19.3, J19.5, J19.7, J20.1, J20.3, J20.5, J20.7, J21.1, J21.3, J21.5, J21.7, J22.1, J22.3, J22.5, J22.7, R9.2, U9.16 (VMot), U10.16 (VMot), U11.16 (VMot), U12.16 (VMot), U13.16 (VMot), U14.16 (VMot)
Vin: C1.1, C5.2, D1.1 (K), U1.38 (VIN), U3.38 (VIN)
X_CS: U5.3 (QD), U9.4 (MS3(CS))
X_Diag1: J5.6, U9.17 (Diag1)
X_Dir: U5.1 (QB), U9.8 (Dir)
X_Enable: U5.15 (QA), U9.1 (Enable)
X_Limit: J4.6, J6.4 (1), U3.27 (IO33)
X_Step: U5.2 (QC), U9.7 (Step)
Y_CS: U5.7 (QH), U10.4 (MS3(CS))
Y_Diag1: J5.5, U10.17 (Diag1)
Y_Dir: U5.5 (QF), U10.8 (Dir)
Y_Enable: U5.4 (QE), U10.1 (Enable)
Y_Limit: J4.5, J6.5 (2), U3.26 (IO32)
Y_Step: U5.6 (QG), U10.7 (Step)
Z_CS: U7.3 (QD), U11.4 (MS3(CS))
Z_Diag1: J5.4, U11.17 (Diag1)
Z_Dir: U2.7 (Qb), U11.8 (Dir)
Z_Enable: U2.4 (Qa), U11.1 (Enable)
Z_Limit: J4.4, J6.6 (3), R8.1, U3.25 (IO35)
Z_Steo: U2.9 (Qc), U11.7 (Step)

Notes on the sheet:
84223C
GRBL ESP32
Motor Config
I2C Shift Registers
SD Card
IO from GRBL and Toarch
Motor Drivers
Power
CNC I/O Modules
Torch Height
TODO remove r5 r6 r7 r8, divider bug bridged gpio34 between

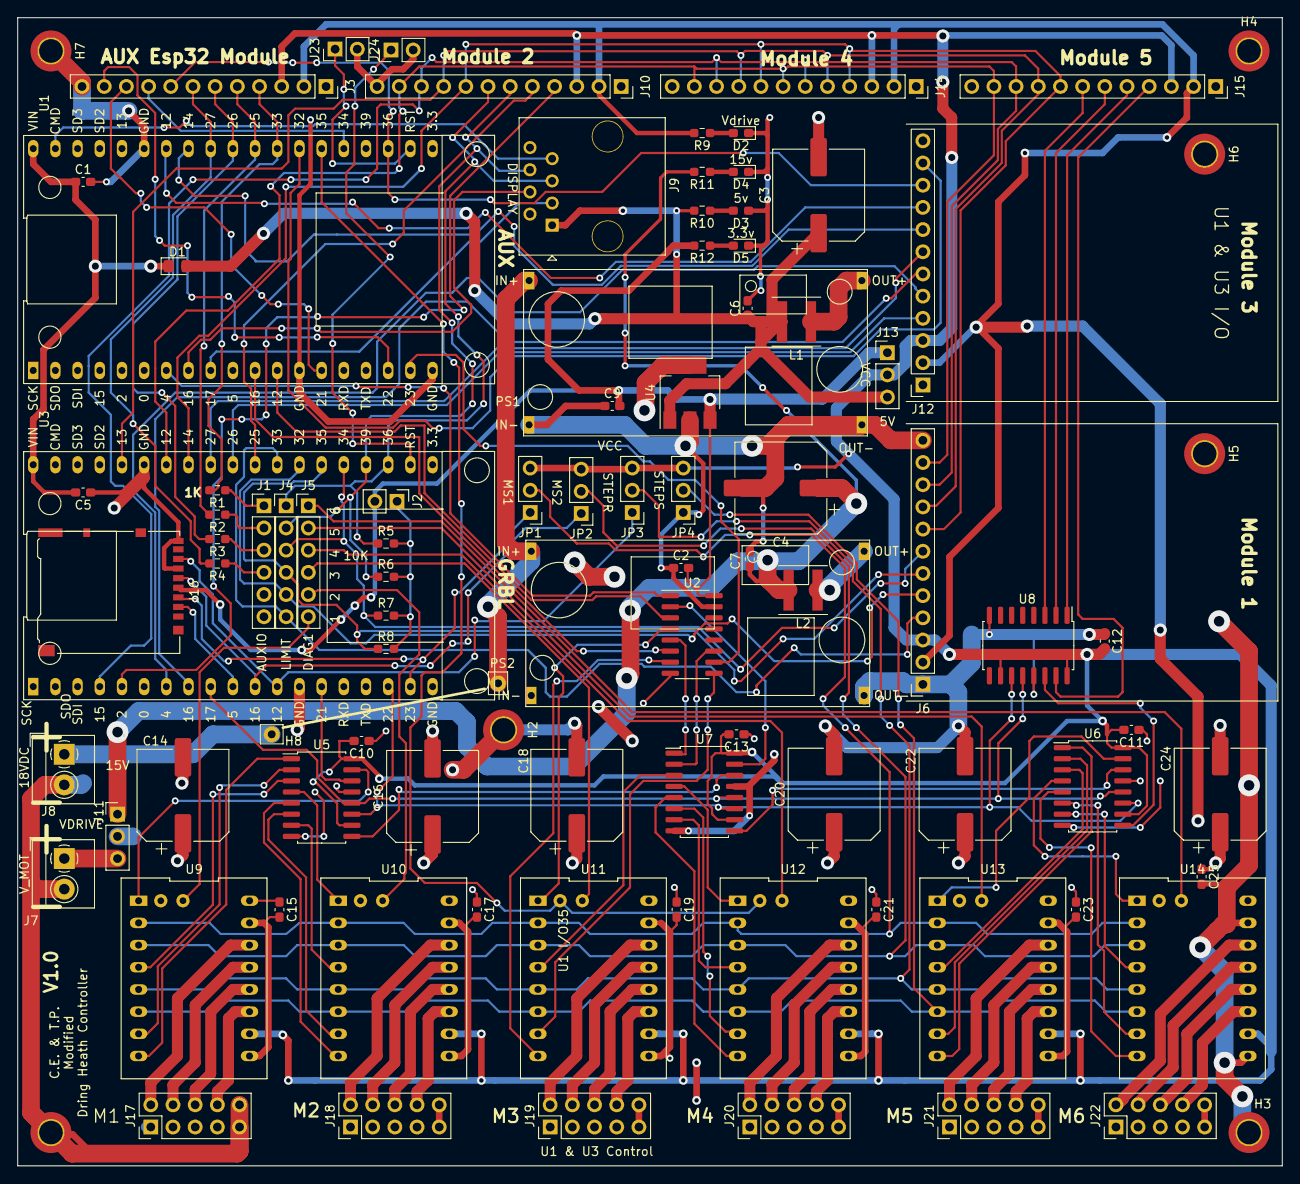
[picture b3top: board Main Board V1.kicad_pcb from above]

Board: 2 copper layers, 144.8 x 131.4 mm, 96 parts (0 on the bottom side), 132 nets.
